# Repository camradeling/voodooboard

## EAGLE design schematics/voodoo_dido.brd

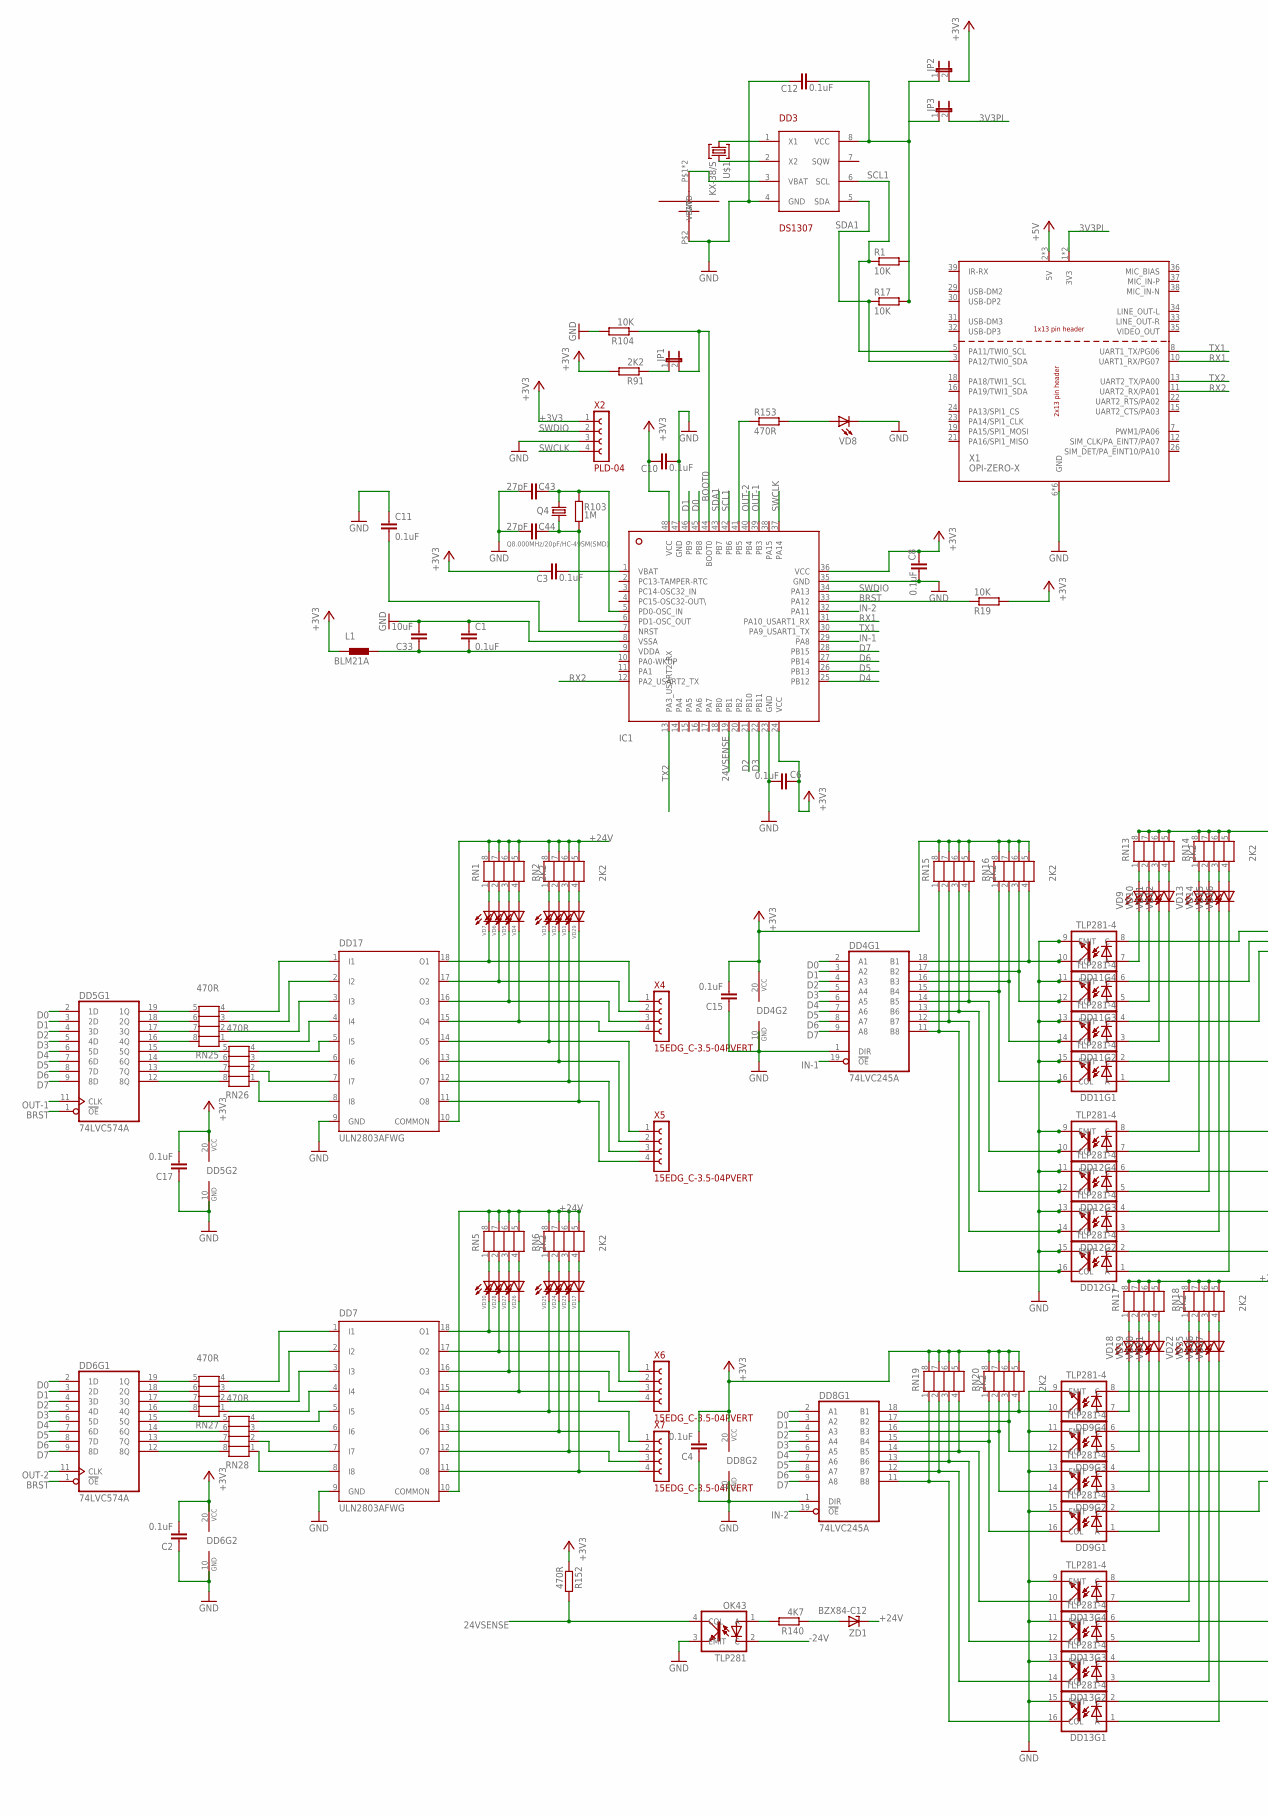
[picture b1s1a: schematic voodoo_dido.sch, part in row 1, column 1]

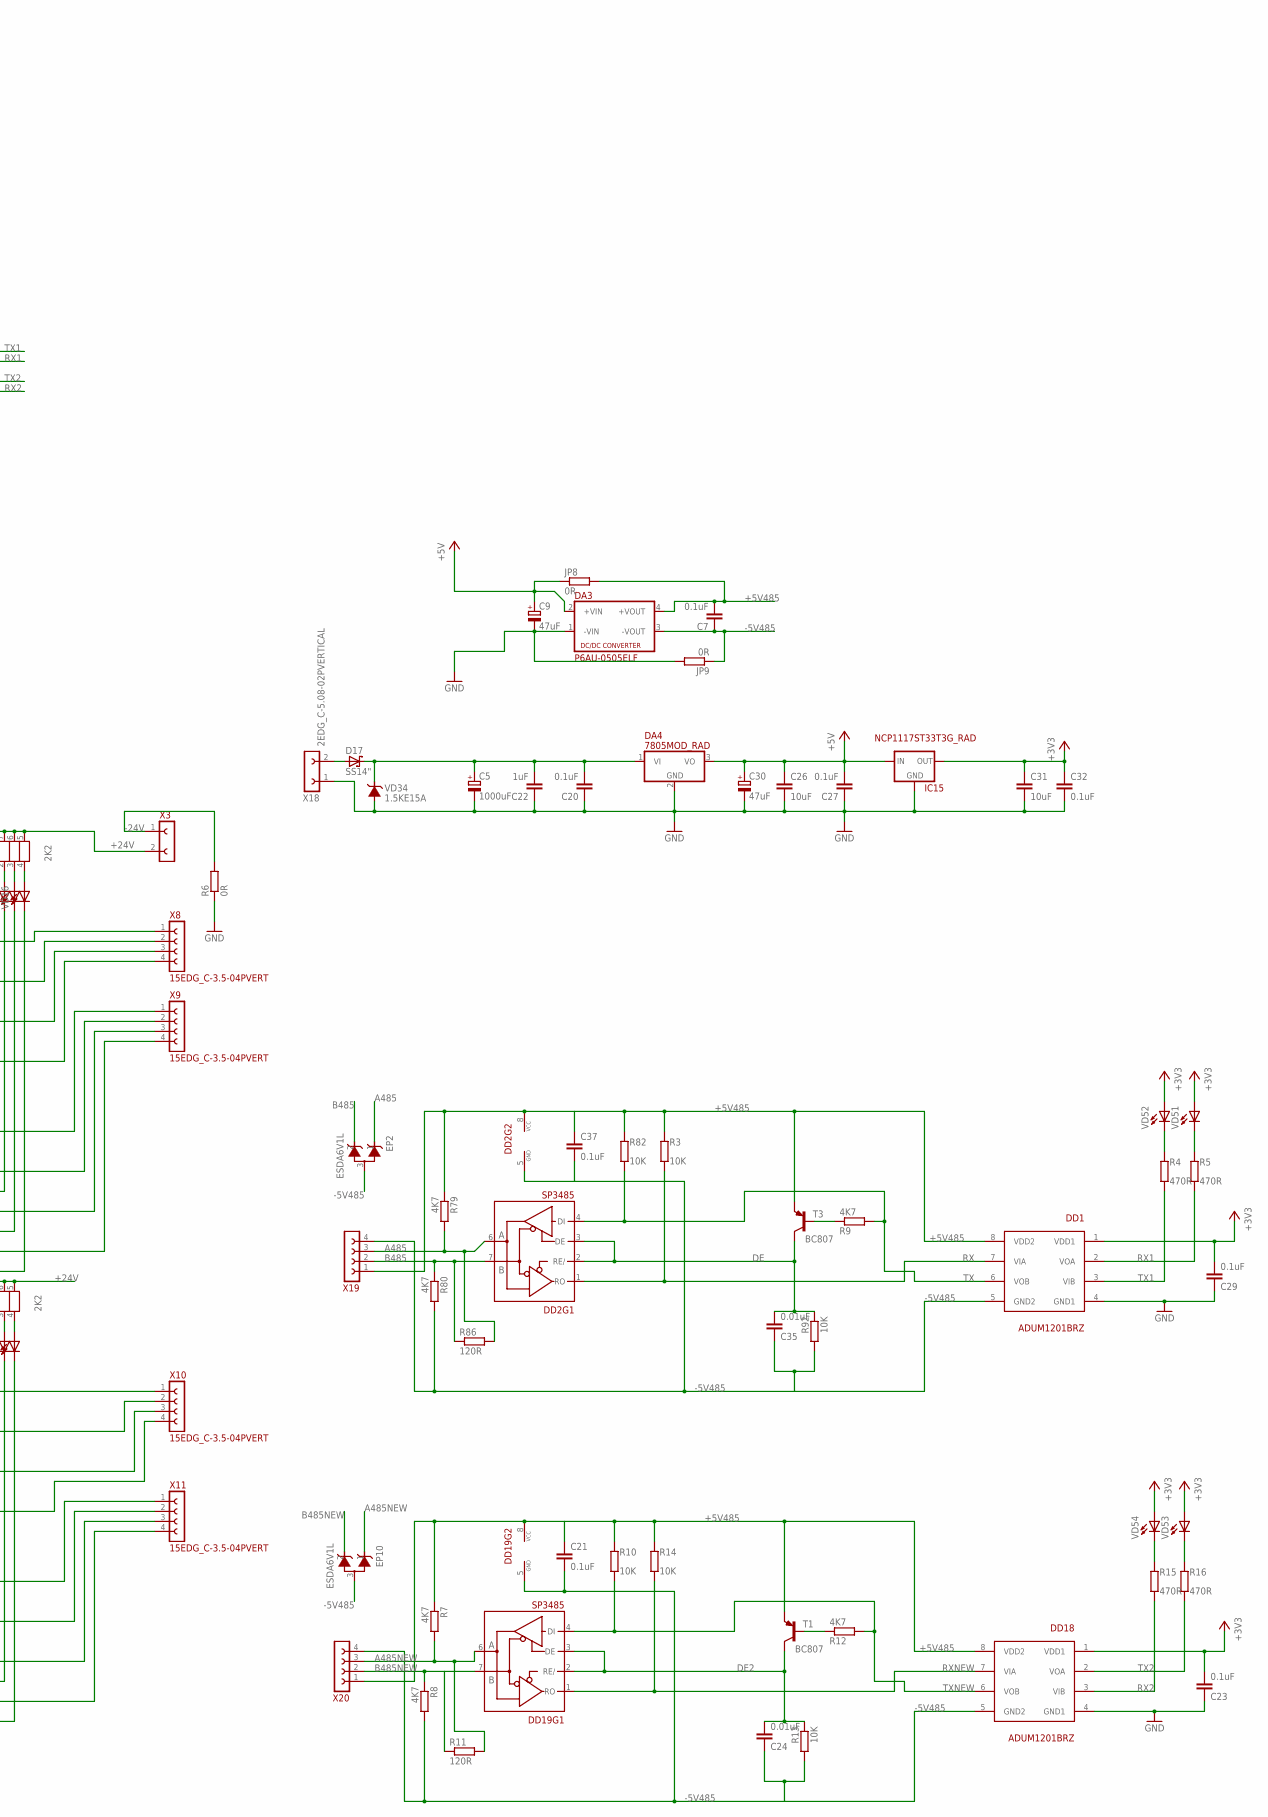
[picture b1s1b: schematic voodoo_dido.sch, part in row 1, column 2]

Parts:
B1: BH840
C1, C3, C6, C8, C10, C11, C12: 0.1uF; 0603MOD
C2, C4, C7, C15, C17, C20, C21, C23, C27, C29, C32, C37: 0.1uF; 0805MOD
C5: 1000uF; 150CLZ-1010
C9, C30: 47uF; SMC_B
C22: 1uF; 0805MOD
C24, C35: 0.01uF; 0805MOD
C26, C31, C33: 10uF; C1206
C43, C44: 27pF; 0805MOD
D17: SS14"; MLL-41
DA3: P6AU-0505ELF; SIP4
DA4: 7805MOD_RAD; TO220RAD
DD1, DD18: ADUM1201BRZ; SO08
DD2, DD19: SP3485; SO08
DD3: DS1307; SO08
DD4, DD8: 74LVC245A; SO20W
DD5, DD6: 74LVC574A; SO20W
DD7, DD17: ULN2803AFWG; SO18
DD9, DD11, DD12, DD13: TLP281-4
EP2, EP10: ESDA6V1L; SOT23
IC1: STM32F103C8T6; TQFP48
IC15: NCP1117ST33T3G_RAD; SOT223_PCBRAD
JP1, JP2, JP3: JP1E; JP1
JP8, JP9: 0R; 0805MOD
L1: BLM21A; 1206/0603
OK43: TLP281
Q4: Q8.000MHz/20pF/HC-49SM(SMD); HC49UP
R1, R3, R10, R13, R14, R17, R19, R82, R92, R104: 10K; 0805MOD
R4, R5, R15, R16, R152, R153: 470R; 0805MOD
R6: 0R; 0805MOD
R7, R8, R9, R12, R79, R80, R140: 4K7; 0805MOD
R11, R86: 120R; 0805MOD
R91: 2K2; 0805MOD
R103: 1M; 0805MOD
RN1, RN2, RN5, RN6, RN13, RN14, RN15, RN16, RN17, RN18, RN19, RN20: 2K2; CAT16-J4
RN25, RN26, RN27, RN28: 470R; CAT16-J4
T1, T3: BC807; SOT23-BEC
U$1: KX-38/S; KX-38
VD1, VD2, VD3, VD4, VD5, VD6, VD7, VD17, VD23, VD24, VD25, VD26, VD27, VD28, VD29, VD30: KP-2012EC(RED); CHIP-LED0805
VD8, VD9, VD10, VD11, VD12, VD13, VD14, VD15, VD16, VD18, VD19, VD20, VD21, VD22, VD35, VD36, VD37, VD51, VD52, VD53, VD54: KP-2012SGC(GREEN); CHIP-LED0805
VD34: 1.5KE15A; MSORB_41A-04_D
X1: OPI-ZERO-X; OPI0X
X2: PLD-04; PLD04
X3, X18: 2EDG_C-5.08-02PVERTICAL; 2EDGVC-5.08-02P
X4, X5, X6, X7, X8, X9, X10, X11, X19, X20: 15EDG_C-3.5-04PVERT; 15EDGVC-3.5-04P
ZD1: BZX84-C12; SOT23

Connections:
3V3PI: JP3.2, X1.1 (3V3), X1.17 (3V3)
24VSENSE: IC1.19 (PB1), OK43.4 (COL), R152.P$2 (2)
+3V3: C2.P$2 (2), C3.1, C4.P$2 (2), C6.1, C8.1, C10.1, C15.P$2 (2), C17.P$2 (2), C23.P$2 (2), C29.P$2 (2), C31.1, C32.P$1 (1), DD1.1 (VDD1), DD4.20 (VCC), DD5.20 (VCC), DD6.20 (VCC), DD8.20 (VCC), DD18.1 (VDD1), IC1.24 (VDD), IC1.36 (VDD), IC1.48 (VDD), IC15.2 (OUT), JP2.2, L1.1, R19.P$2 (2), R91.P$2 (2), R152.P$1 (1), RN15.5, RN15.6, RN15.7, RN15.8, RN16.5, RN16.6, RN16.7, RN16.8, RN19.5, RN19.6, RN19.7, RN19.8, RN20.5, RN20.6, RN20.7, RN20.8, VD51.A, VD52.A, VD53.A, VD54.A, X2.1
+5V: C9.+, C26.1, C27.P$2 (2), C30.+, DA3.2 (+VIN), DA4.3 (VO), IC15.3 (IN), JP8.P$1 (1), X1.2 (5V), X1.4 (5V), X1.27 (5V)
+5V485: C7.P$2 (2), C21.P$1 (1), C37.P$1 (1), DA3.4 (+VOUT), DD1.8 (VDD2), DD2.8 (VCC), DD18.8 (VDD2), DD19.8 (VCC), JP8.P$2 (2), R3.P$1 (1), R7.P$1 (1), R10.P$1 (1), R14.P$1 (1), R79.P$1 (1), R82.P$1 (1), T1.E, T3.E, X19.1, X20.1
+24V: DD7.10 (COMMON), DD17.10 (COMMON), RN1.5, RN1.6, RN1.7, RN1.8, RN2.5, RN2.6, RN2.7, RN2.8, RN5.5, RN5.6, RN5.7, RN5.8, RN6.5, RN6.6, RN6.7, RN6.8, RN13.5, RN13.6, RN13.7, RN13.8, RN14.5, RN14.6, RN14.7, RN14.8, RN17.5, RN17.6, RN17.7, RN17.8, RN18.5, RN18.6, RN18.7, RN18.8, X3.2, ZD1.3 (C)
-5V485: C7.P$1 (1), C21.P$2 (2), C24.P$1 (1), C35.P$1 (1), C37.P$2 (2), DA3.3 (-VOUT), DD1.5 (GND2), DD2.5 (GND), DD18.5 (GND2), DD19.5 (GND), EP2.3, EP10.3, JP9.P$1 (1), R8.P$2 (2), R13.P$2 (2), R80.P$2 (2), R92.P$2 (2), X19.4, X20.4
-24V: OK43.2 (C), R6.P$2 (2), X3.1
A485: DD2.6 (A), EP2.1, R79.P$2 (2), R86.P$2 (2), X19.3
A485NEW: DD19.6 (A), EP10.1, R7.P$2 (2), R11.P$2 (2), X20.3
B485: DD2.7 (B), EP2.2, R80.P$1 (1), R86.P$1 (1), X19.2
B485NEW: DD19.7 (B), EP10.2, R8.P$1 (1), R11.P$1 (1), X20.2
BOOT0: IC1.44 (BOOT0), JP1.2, R104.P$1 (1)
BRST: DD5.1 (!OE), DD6.1 (!OE), IC1.33 (PA12), R19.P$1 (1)
D0: DD4.2 (A1), DD5.2 (1D), DD6.2 (1D), DD8.2 (A1), IC1.45 (PB8)
D1: DD4.3 (A2), DD5.3 (2D), DD6.3 (2D), DD8.3 (A2), IC1.46 (PB9)
D2: DD4.4 (A3), DD5.4 (3D), DD6.4 (3D), DD8.4 (A3), IC1.21 (PB10)
D3: DD4.5 (A4), DD5.5 (4D), DD6.5 (4D), DD8.5 (A4), IC1.22 (PB11)
D4: DD4.6 (A5), DD5.6 (5D), DD6.6 (5D), DD8.6 (A5), IC1.25 (PB12)
D5: DD4.7 (A6), DD5.7 (6D), DD6.7 (6D), DD8.7 (A6), IC1.26 (PB13)
D6: DD4.8 (A7), DD5.8 (7D), DD6.8 (7D), DD8.8 (A7), IC1.27 (PB14)
D7: DD4.9 (A8), DD5.9 (8D), DD6.9 (8D), DD8.9 (A8), IC1.28 (PB15)
DE: C35.P$2 (2), DD2.2 (RE/), DD2.3 (DE), R92.P$1 (1), T3.C
DE2: C24.P$2 (2), DD19.2 (RE/), DD19.3 (DE), R13.P$1 (1), T1.C
GND: B1.P$2 (GND), C1.1, C2.P$1 (1), C4.P$1 (1), C5.-, C6.2, C8.2, C9.-, C10.2, C11.1, C12.1, C15.P$1 (1), C17.P$1 (1), C20.P$1 (1), C22.P$1 (1), C23.P$1 (1), C26.2, C27.P$1 (1), C29.P$1 (1), C30.-, C31.2, C32.P$2 (2), C33.2, C43.P$2 (2), C44.P$2 (2), DA3.1 (-VIN), DA4.2 (GND), DD1.4 (GND1), DD3.4 (GND), DD4.1 (DIR), DD4.10 (GND), DD5.10 (GND), DD6.10 (GND), DD7.9 (GND), DD8.1 (DIR), DD8.10 (GND), DD9.9 (EMIT), DD9.11 (EMIT), DD9.13 (EMIT), DD9.15 (EMIT), DD11.9 (EMIT), DD11.11 (EMIT), DD11.13 (EMIT), DD11.15 (EMIT), DD12.9 (EMIT), DD12.11 (EMIT), DD12.13 (EMIT), DD12.15 (EMIT), DD13.9 (EMIT), DD13.11 (EMIT), DD13.13 (EMIT), DD13.15 (EMIT), DD17.9 (GND), DD18.4 (GND1), IC1.8 (VSSA), IC1.23 (VSS), IC1.35 (VSS), IC1.47 (VSS), IC15.1 (GND), JP9.P$2 (2), OK43.3 (EMIT), R6.P$1 (1), R104.P$2 (2), VD8.C, VD34.A, X1.6 (GND), X1.9 (GND), X1.14 (GND), X1.20 (GND), X1.25 (GND), X1.28 (GND), X2.3, X18.1
IN-1: DD4.19 (!OE), IC1.29 (PA8)
IN-2: DD8.19 (!OE), IC1.32 (PA11)
unnamed: DD8.18 (B1), DD9.10 (COL), RN20.4
unnamed: DD11.7 (A), VD9.C
unnamed: C5.+, C20.P$2 (2), C22.P$2 (2), D17.K (C), DA4.1 (VI), VD34.С (C)
unnamed: R4.P$1 (1), VD52.C
unnamed: R5.P$1 (1), VD51.C
unnamed: IC1.41 (PB5), R153.P$1 (1)
unnamed: DD8.17 (B2), DD9.12 (COL), RN20.3
unnamed: C11.2, IC1.7 (NRST)
unnamed: DD8.16 (B3), DD9.14 (COL), RN20.2
unnamed: D17.A, X18.2
unnamed: DD3.1 (X1), U$1.1
unnamed: DD8.15 (B4), DD9.16 (COL), RN20.1
unnamed: DD9.7 (A), VD18.C
unnamed: DD9.5 (A), VD19.C
unnamed: DD3.2 (X2), U$1.2
unnamed: B1.P$1 (VBAT), B1.P$3 (VBAT), DD3.3 (VBAT)
unnamed: C12.2, DD3.8 (VCC), JP2.1, JP3.1, R1.P$2 (2), R17.P$2 (2)
unnamed: C3.2, IC1.1 (VBAT)
unnamed: DD9.3 (A), VD20.C
unnamed: DD11.5 (A), VD10.C
unnamed: DD11.3 (A), VD11.C
unnamed: DD4.18 (B1), DD11.10 (COL), RN16.4
unnamed: DD11.1 (A), VD12.C
unnamed: RN13.1, VD9.A
unnamed: RN13.2, VD10.A
unnamed: RN13.3, VD11.A
unnamed: DD4.14 (B5), DD12.10 (COL), RN15.4
unnamed: DD4.13 (B6), DD12.12 (COL), RN15.3
unnamed: DD4.12 (B7), DD12.14 (COL), RN15.2
unnamed: RN13.4, VD12.A
unnamed: RN14.1, VD13.A
unnamed: RN14.2, VD14.A
unnamed: RN14.3, VD15.A
unnamed: RN14.4, VD16.A
unnamed: DD12.8 (C), X9.1
unnamed: DD12.6 (C), X9.2
unnamed: DD4.11 (B8), DD12.16 (COL), RN15.1
unnamed: DD12.4 (C), X9.3
unnamed: DD12.2 (C), X9.4
unnamed: DD9.1 (A), VD21.C
unnamed: DD12.7 (A), VD13.C
unnamed: DD12.5 (A), VD14.C
unnamed: DD12.3 (A), VD15.C
unnamed: DD12.1 (A), VD16.C
unnamed: DD11.8 (C), X8.1
unnamed: RN17.1, VD18.A
unnamed: DD4.17 (B2), DD11.12 (COL), RN16.3
unnamed: DD4.16 (B3), DD11.14 (COL), RN16.2
unnamed: DD4.15 (B4), DD11.16 (COL), RN16.1
unnamed: DD11.6 (C), X8.2
unnamed: DD11.4 (C), X8.3
unnamed: DD11.2 (C), X8.4
unnamed: RN17.2, VD19.A
unnamed: RN17.3, VD20.A
unnamed: RN17.4, VD21.A
unnamed: RN18.1, VD22.A
unnamed: RN18.2, VD35.A
unnamed: RN18.3, VD36.A
unnamed: RN18.4, VD37.A
unnamed: DD13.8 (C), X11.1
unnamed: DD13.6 (C), X11.2
unnamed: DD13.4 (C), X11.3
unnamed: DD13.2 (C), X11.4
unnamed: DD13.7 (A), VD22.C
unnamed: DD13.5 (A), VD35.C
unnamed: DD13.3 (A), VD36.C
unnamed: DD13.1 (A), VD37.C
unnamed: DD9.8 (C), X10.1
unnamed: DD9.6 (C), X10.2
unnamed: DD9.4 (C), X10.3
unnamed: DD9.2 (C), X10.4
unnamed: DD8.14 (B5), DD13.10 (COL), RN19.4
unnamed: DD8.13 (B6), DD13.12 (COL), RN19.3
unnamed: DD8.12 (B7), DD13.14 (COL), RN19.2
unnamed: DD8.11 (B8), DD13.16 (COL), RN19.1
unnamed: DD5.19 (1Q), RN25.5
unnamed: DD17.8 (I8), RN26.1
unnamed: DD17.7 (I7), RN26.2
unnamed: DD17.6 (I6), RN26.3
unnamed: DD17.5 (I5), RN26.4
unnamed: C1.2, C33.1, IC1.9 (VDDA), L1.2
unnamed: DD17.4 (I4), RN25.1
unnamed: DD17.3 (I3), RN25.2
unnamed: DD17.2 (I2), RN25.3
unnamed: R9.P$1 (1), T3.B
unnamed: DD17.1 (I1), RN25.4
unnamed: R153.P$2 (2), VD8.A
unnamed: R12.P$1 (1), T1.B
unnamed: R140.P$1 (1), ZD1.1 (A)
unnamed: JP1.1, R91.P$1 (1)
unnamed: R15.P$1 (1), VD54.C
unnamed: R16.P$1 (1), VD53.C
unnamed: OK43.1 (A), R140.P$2 (2)
unnamed: DD5.15 (5Q), RN26.5
unnamed: DD6.19 (1Q), RN27.5
unnamed: DD5.18 (2Q), RN25.6
unnamed: DD5.17 (3Q), RN25.7
unnamed: DD5.16 (4Q), RN25.8
unnamed: DD5.14 (6Q), RN26.6
unnamed: DD6.18 (2Q), RN27.6
unnamed: DD6.17 (3Q), RN27.7
unnamed: DD6.16 (4Q), RN27.8
unnamed: DD6.15 (5Q), RN28.5
unnamed: DD17.18 (O1), VD7.C, X4.1
unnamed: DD17.17 (O2), VD6.C, X4.2
unnamed: DD17.16 (O3), VD5.C, X4.3
unnamed: DD17.15 (O4), VD4.C, X4.4
unnamed: DD6.14 (6Q), RN28.6
unnamed: DD6.13 (7Q), RN28.7
unnamed: DD6.12 (8Q), RN28.8
unnamed: DD7.8 (I8), RN28.1
unnamed: DD7.7 (I7), RN28.2
unnamed: DD7.6 (I6), RN28.3
unnamed: DD7.5 (I5), RN28.4
unnamed: DD7.4 (I4), RN27.1
unnamed: DD17.14 (O5), VD3.C, X5.1
unnamed: DD17.13 (O6), VD2.C, X5.2
unnamed: DD7.3 (I3), RN27.2
unnamed: RN1.1, VD7.A
unnamed: DD7.2 (I2), RN27.3
unnamed: DD7.1 (I1), RN27.4
unnamed: DD17.12 (O7), VD1.C, X5.3
unnamed: DD17.11 (O8), VD29.C, X5.4
unnamed: DD5.13 (7Q), RN26.7
unnamed: RN1.2, VD6.A
unnamed: DD5.12 (8Q), RN26.8
unnamed: RN1.3, VD5.A
unnamed: DD7.18 (O1), VD30.C, X6.1
unnamed: RN1.4, VD4.A
unnamed: DD7.17 (O2), VD28.C, X6.2
unnamed: RN2.1, VD3.A
unnamed: DD7.16 (O3), VD27.C, X6.3
unnamed: DD7.15 (O4), VD26.C, X6.4
unnamed: DD7.14 (O5), VD25.C, X7.1
unnamed: DD7.13 (O6), VD24.C, X7.2
unnamed: DD7.12 (O7), VD23.C, X7.3
unnamed: RN2.2, VD2.A
unnamed: RN2.3, VD1.A
unnamed: RN2.4, VD29.A
unnamed: C43.P$1 (1), IC1.5 (PD0-OSC_IN), Q4.2, R103.P$2 (2)
unnamed: C44.P$1 (1), IC1.6 (PD1-OSC_OUT), Q4.1, R103.P$1 (1)
unnamed: DD7.11 (O8), VD17.C, X7.4
unnamed: RN5.1, VD30.A
unnamed: RN5.2, VD28.A
unnamed: RN5.3, VD27.A
unnamed: RN5.4, VD26.A
unnamed: RN6.1, VD25.A
unnamed: RN6.2, VD24.A
unnamed: RN6.3, VD23.A
unnamed: RN6.4, VD17.A
OUT-1: DD5.11 (CLK), IC1.39 (PB3)
OUT-2: DD6.11 (CLK), IC1.40 (PB4)
PA7: IC1.17 (PA7)
RX: DD1.7 (VIA), DD2.1 (RO), R3.P$2 (2)
RX1: DD1.2 (VOA), IC1.31 (PA10_USART1_RX), R5.P$2 (2), X1.10 (UART1_RX/PG07)
RX2: DD18.2 (VOA), IC1.12 (PA2_USART2_TX), R16.P$2 (2), X1.11 (UART2_RX/PA01)
RXNEW: DD18.7 (VIA), DD19.1 (RO), R14.P$2 (2)
SCL1: DD3.6 (SCL), IC1.42 (PB6), R1.P$1 (1), X1.5 (PA11/TWI0_SCL)
SDA1: DD3.5 (SDA), IC1.43 (PB7), R17.P$1 (1), X1.3 (PA12/TWI0_SDA)
SWCLK: IC1.37 (PA14), X2.4
SWDIO: IC1.34 (PA13), X2.2
TX: DD1.6 (VOB), DD2.4 (DI), R9.P$2 (2), R82.P$2 (2)
TX1: DD1.3 (VIB), IC1.30 (PA9_USART1_TX), R4.P$2 (2), X1.8 (UART1_TX/PG06)
TX2: DD18.3 (VIB), IC1.13 (PA3_USART2_RX), R15.P$2 (2), X1.13 (UART2_TX/PA00)
TXNEW: DD18.6 (VOB), DD19.4 (DI), R10.P$2 (2), R12.P$2 (2)

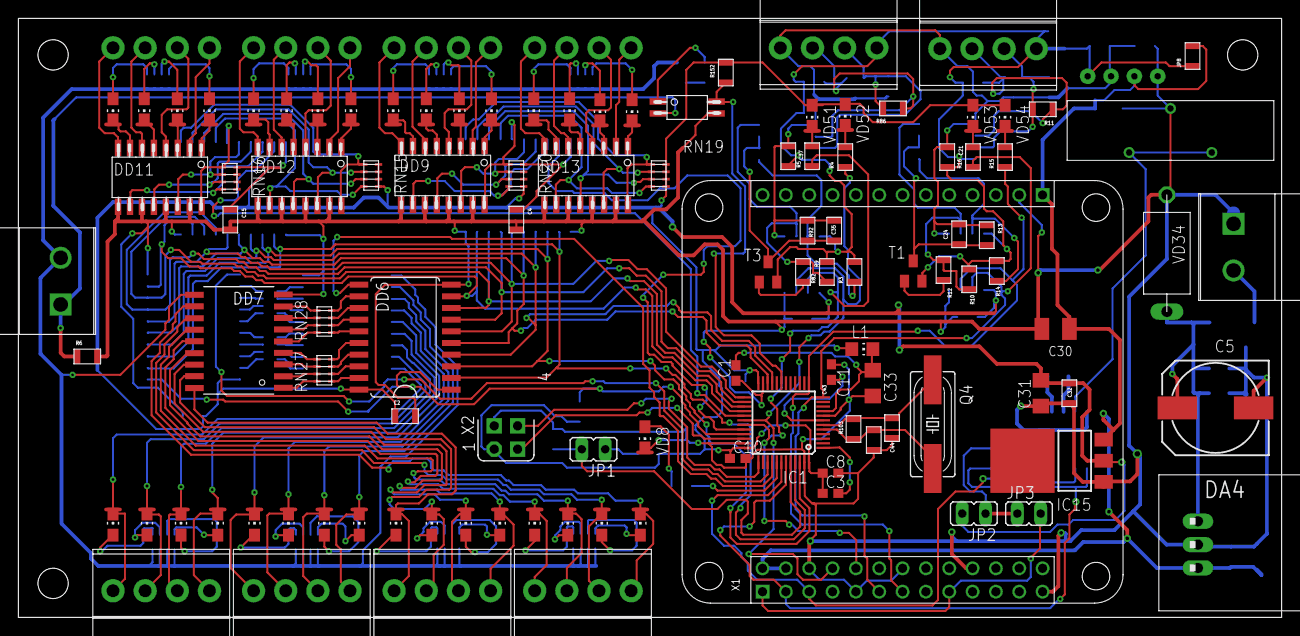
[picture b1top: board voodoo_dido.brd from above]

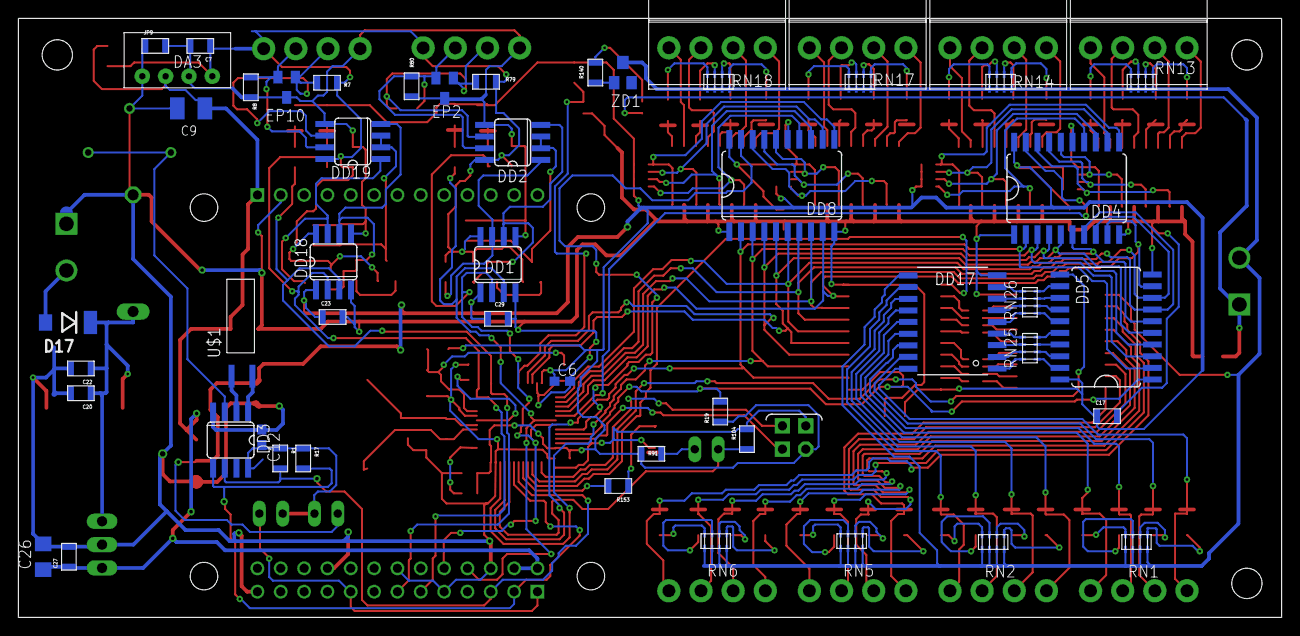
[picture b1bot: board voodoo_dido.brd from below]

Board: 2 copper layers, 137.5 x 65.2 mm, 161 parts (52 on the bottom side), 191 nets.

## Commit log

2021-04-25 некоторые исправления
2021-04-25 все добавлено
2021-05-10 FreeRTOS kernel repository is enough
2021-05-10 cleanup
2021-05-10 modbus as separate lib
2024-09-01 fixing
2024-10-13 working on the board
2024-10-13 added datasheets
2024-10-13 formatting
2024-10-13 more formatting
2024-10-13 more accurate defines
2024-10-13 some more cleanup
